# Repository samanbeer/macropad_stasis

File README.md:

# My MacroPad Project

This is custom 3×3 macropad PCB built with KiCad. It runs with Seeed Studio XIAO RP2040 microcontroller, uses Cherry MX switches and t has RGB lights with SK6812 MINI-E LEDs.

## About This Project

I have done PCB design before, but I wanted to do something more hard like adding MCU, RGB LEDs, and a matrix connection. 
I learned key matrix wiring with diodes, level-shifting logic with the 74AHCT125 processor, PCB routing around an MCU and KiCad in general. 
Also I learned a lot from MarkDown syntax.
I will use this for switching apps, custom scripts in some apps like VsCode for pushing new code to github etc...
The routing was pretty easy, just time consuming but I really enjoed making traces.

## Project Structure

- **[KiCAD_project/](KiCAD_project/)** 
  - `KiCAD_project.kicad_pcb` 
  - `KiCAD_project.kicad_sch` 
  - `KiCAD_project.kicad_pro` 
  - **[output/](KiCAD_project/output/)** 
  - **[OPL_Kicad_Library-master/](KiCAD_project/OPL_Kicad_Library-master/)**
  - **[kicad-libraries-master/](KiCAD_project/kicad-libraries-master/)** 
  - **[kicad_care_package/](KiCAD_project/kicad_care_package/)** 
  - **[KiCAD_project-backups/](KiCAD_project/KiCAD_project-backups/)** 

- **[CAD/](CAD/)** 
  - `3d_PCB.step` 
  - `housing.stl` 
  - `pcb_only.stl` 
  - `With-PCB_for-render.stl` 
  - `Seeed Studio XIAO RP2040.stl` 
  - **[blender/](CAD/blender/)** 

- **[KiCAD_project/My macroPad-bom.csv](KiCAD_project/My%20macroPad-bom.csv)** - BOM

## Design images

### Schematic

### PCB Layout

### 3D Renderings

#### Rendered PCB

#### PCB without rendering

#### Rendered Housing for PCB

#### Housing for PCB (screenshot from fusion360)

### Real Photos

Project Link: https://stasis.hackclub.com/dashboard/projects/cmosrdxum001301mxc1tzjn15

## Bill of Materials

| Component | Purpose | Qty | Total | Distributor |
| :--- | :--- | :---: | :---: | :--- |
| PCB | Board to solder all components on | 1 | ~$1.40 | JLCPCB |
| Cherry MX Switches | Key switches | 10 | ~$3.00 | AliExpress |
| Capacitor 0.47 µF 0603 | Prevents LED flicker on voltage spikes | 10 | ~$0.50 | Farnell |
| Diode 1N4148 | Key matrix diodes for preventing ghosting | 10 | ~$2.15 | Farnell |
| SN74AHCT125N | Voltage level-shifter for RGB LED | 1 | ~$0.90 | Farnell |
| SK6812 MINI-E | RGB LED | 1 | ~$2.40 | AliExpress |
| Seeed Studio XIAO RP2040 | Main microcontroller | 1 | ~$4.80 | Farnell |

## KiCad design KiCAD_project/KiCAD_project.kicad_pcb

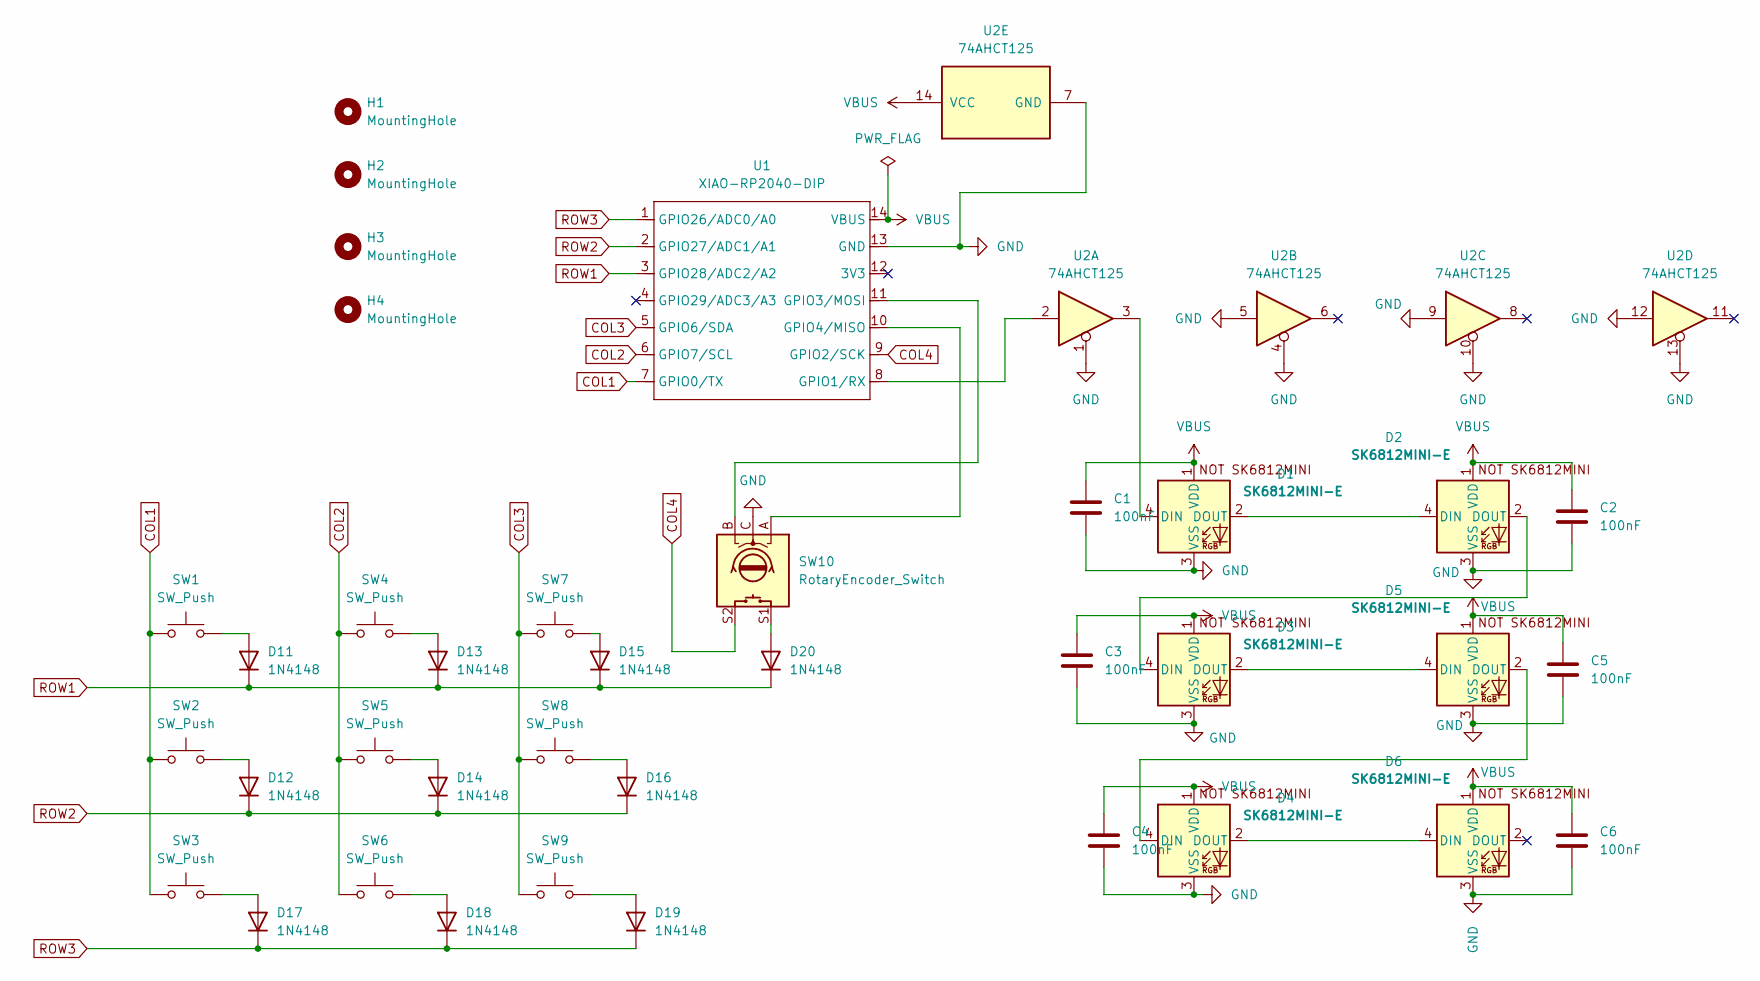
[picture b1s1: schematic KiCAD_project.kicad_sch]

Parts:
C1, C2, C3, C4, C5, C6: 100nF; C_0603_1608Metric
D1, D2, D3, D4, D5, D6: SK6812MINI-E; SK6812MINI-E_fixed
D11, D12, D13, D14, D15, D16, D17, D18, D19, D20: 1N4148; D_DO-35_SOD27_P7.62mm_Horizontal
H1, H2, H3, H4: MountingHole; MountingHole_3.2mm_M3
SW1, SW2, SW3, SW4, SW5, SW6, SW7, SW8, SW9: SW_Push; SW_Cherry_MX_1.00u_PCB
SW10: RotaryEncoder_Switch; RotaryEncoder_Alps_EC11E-Switch_Vertical_H20mm
U1: XIAO-RP2040-DIP
U2: 74AHCT125; DIP-14_W7.62mm

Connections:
COL1: SW1.1, SW2.1, SW3.1, U1.7 (GPIO0/TX)
COL2: SW4.1, SW5.1, SW6.1, U1.6 (GPIO7/SCL)
COL3: SW7.1, SW8.1, SW9.1, U1.5 (GPIO6/SDA)
COL4: SW10.S2, U1.9 (GPIO2/SCK)
GND: C1.2, C2.2, C3.2, C4.2, C5.2, C6.2, D1.3 (VSS), D2.3 (VSS), D3.3 (VSS), D4.3 (VSS), D5.3 (VSS), D6.3 (VSS), SW10.C, U1.13 (GND), U2.1, U2.4, U2.5, U2.7 (GND), U2.9, U2.10, U2.12, U2.13
unnamed: D1.4 (DIN), U2.3
unnamed: D1.2 (DOUT), D2.4 (DIN)
unnamed: D2.2 (DOUT), D3.4 (DIN)
unnamed: D3.2 (DOUT), D5.4 (DIN)
unnamed: D4.4 (DIN), D5.2 (DOUT)
unnamed: D4.2 (DOUT), D6.4 (DIN)
unnamed: D11.2 (A), SW1.2
unnamed: D12.2 (A), SW2.2
unnamed: D13.2 (A), SW4.2
unnamed: D14.2 (A), SW5.2
unnamed: D15.2 (A), SW7.2
unnamed: D16.2 (A), SW8.2
unnamed: D17.2 (A), SW3.2
unnamed: D18.2 (A), SW6.2
unnamed: D19.2 (A), SW9.2
unnamed: D20.2 (A), SW10.S1
unnamed: U1.8 (GPIO1/RX), U2.2
unnamed: SW10.B, U1.11 (GPIO3/MOSI)
unnamed: SW10.A, U1.10 (GPIO4/MISO)
ROW1: D11.1 (K), D13.1 (K), D15.1 (K), D20.1 (K), U1.3 (GPIO28/ADC2/A2)
ROW2: D12.1 (K), D14.1 (K), D16.1 (K), U1.2 (GPIO27/ADC1/A1)
ROW3: D17.1 (K), D18.1 (K), D19.1 (K), U1.1 (GPIO26/ADC0/A0)
VBUS: C1.1, C2.1, C3.1, C4.1, C5.1, C6.1, D1.1 (VDD), D2.1 (VDD), D3.1 (VDD), D4.1 (VDD), D5.1 (VDD), D6.1 (VDD), U1.14 (VBUS), U2.14 (VCC)

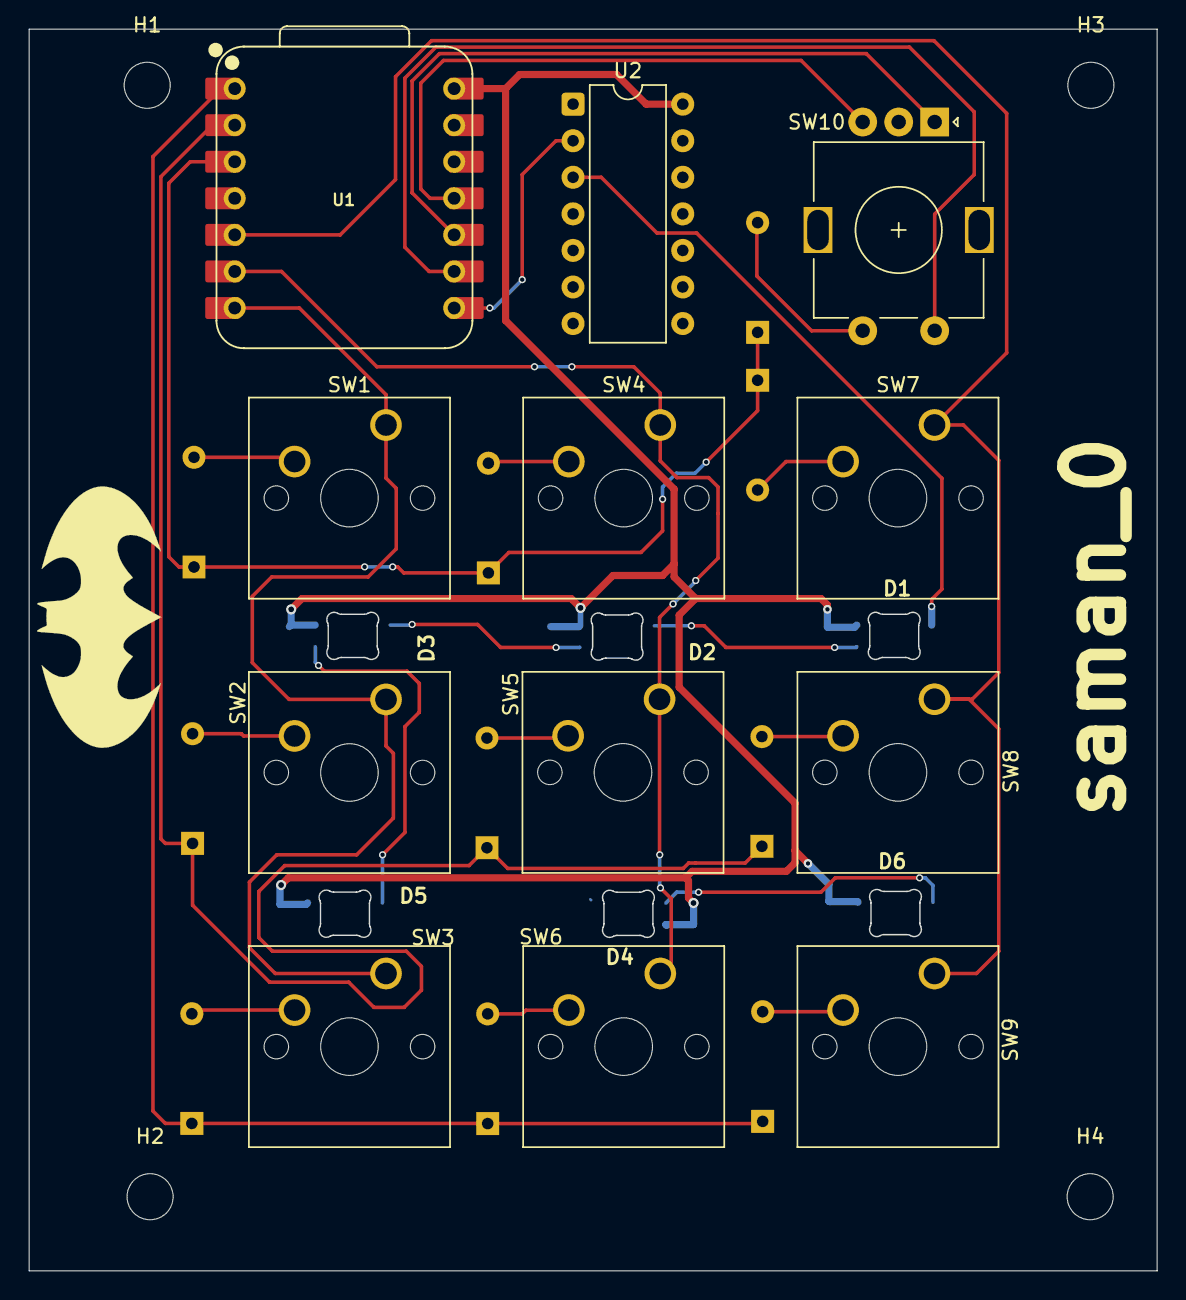
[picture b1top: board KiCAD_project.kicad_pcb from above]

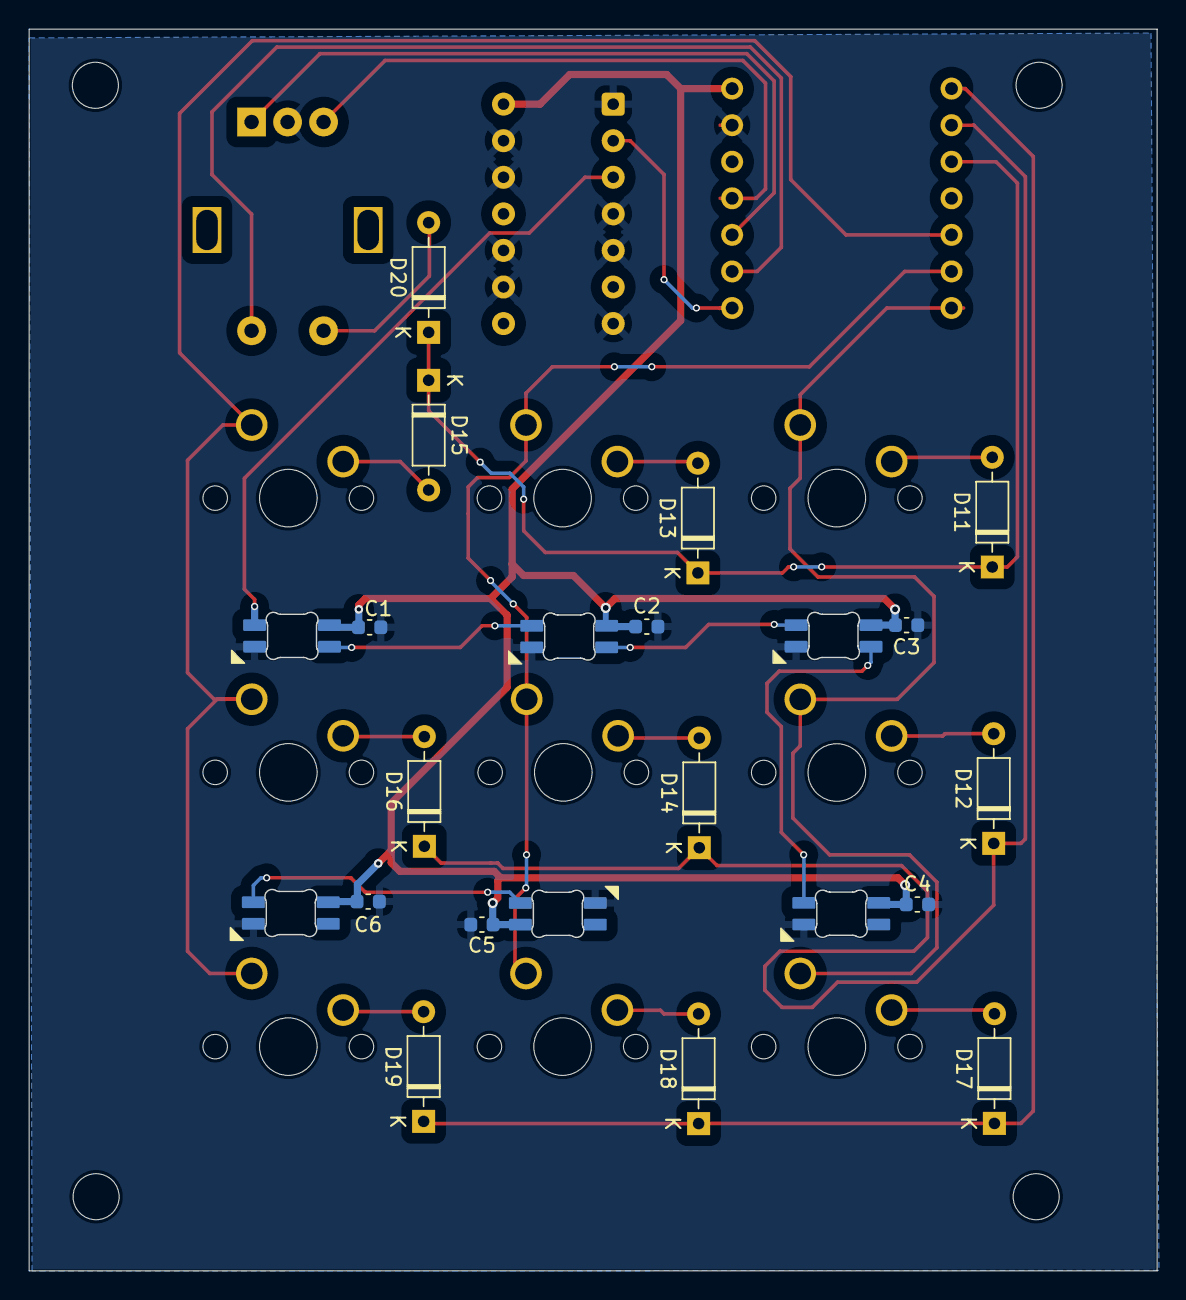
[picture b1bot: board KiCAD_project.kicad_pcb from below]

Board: 2 copper layers, 78.3 x 86.2 mm, 38 parts (16 on the bottom side), 28 nets.

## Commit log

2026-05-05 github setup
2026-05-07 day 1
2026-05-09 added images and BOM into readme.md
2026-05-16 Added edited PCB and CAD
2026-05-16 Update README with rendered housing images
2026-05-27 image update
2026-06-11 README update for review
2026-06-11 Update for README for revieq
2026-06-11 Fixed BOM table
2026-06-13 Update BOM CSV to match README BOM structure and clean links
2026-06-22 Add IRL photos to README
